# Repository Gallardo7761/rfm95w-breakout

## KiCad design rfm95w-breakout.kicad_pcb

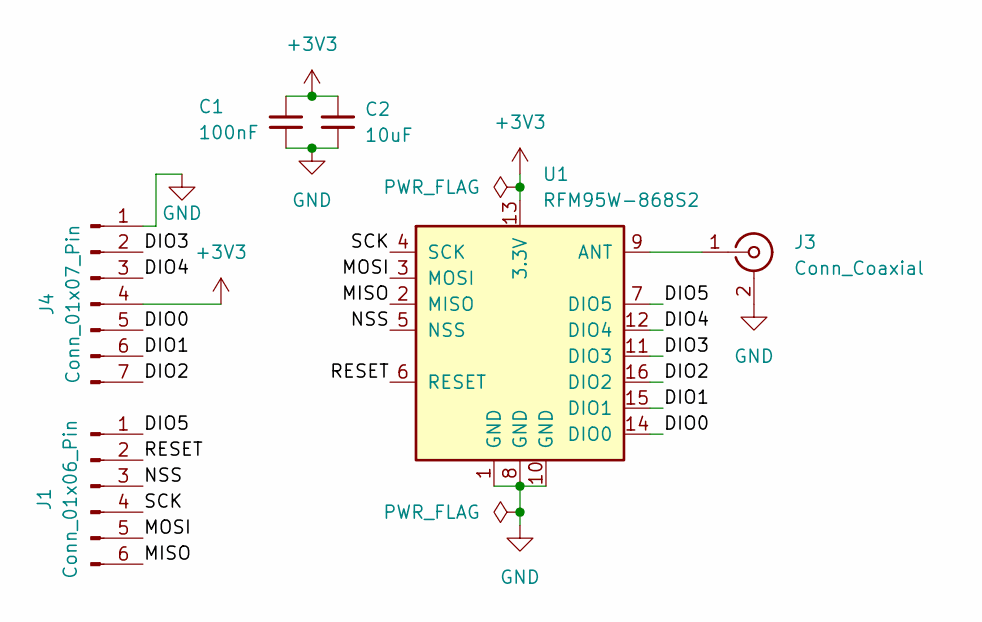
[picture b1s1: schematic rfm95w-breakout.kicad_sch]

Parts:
C1: 100nF; C_0805_2012Metric
C2: 10uF; C_0805_2012Metric
J1: Conn_01x06_Pin; PinHeader_1x06_P2.54mm_Vertical
J3: Conn_Coaxial; SMA_Amphenol_132289_EdgeMount
J4: Conn_01x07_Pin; PinHeader_1x07_P2.54mm_Vertical
U1: RFM95W-868S2; HOPERF_RFM69HW

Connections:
+3V3: C1.1, C2.1, J4.4, U1.13 (3.3V)
/DIO0: J4.5, U1.14 (DIO0)
/DIO1: J4.6, U1.15 (DIO1)
/DIO2: J4.7, U1.16 (DIO2)
/DIO3: J4.2, U1.11 (DIO3)
/DIO4: J4.3, U1.12 (DIO4)
/DIO5: J1.1, U1.7 (DIO5)
/MISO: J1.6, U1.2 (MISO)
/MOSI: J1.5, U1.3 (MOSI)
/NSS: J1.3, U1.5 (NSS)
/RESET: J1.2, U1.6 (RESET)
/SCK: J1.4, U1.4 (SCK)
GND: C1.2, C2.2, J3.2 (Ext), J4.1, U1.1 (GND), U1.8 (GND), U1.10 (GND)
unnamed: J3.1 (In), U1.9 (ANT)

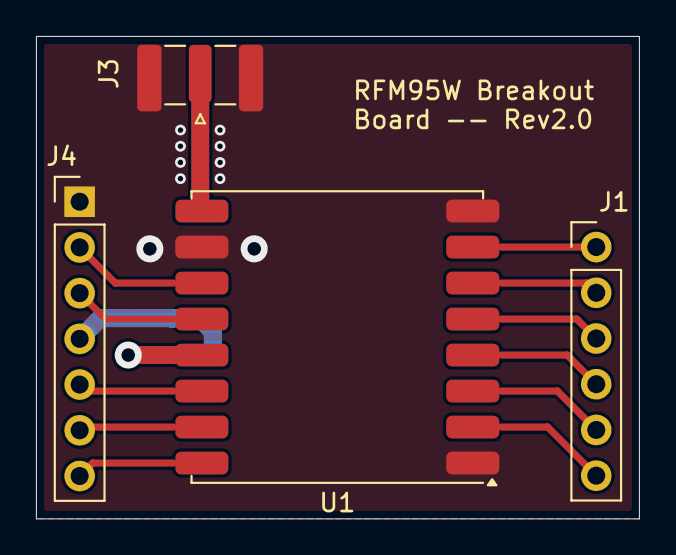
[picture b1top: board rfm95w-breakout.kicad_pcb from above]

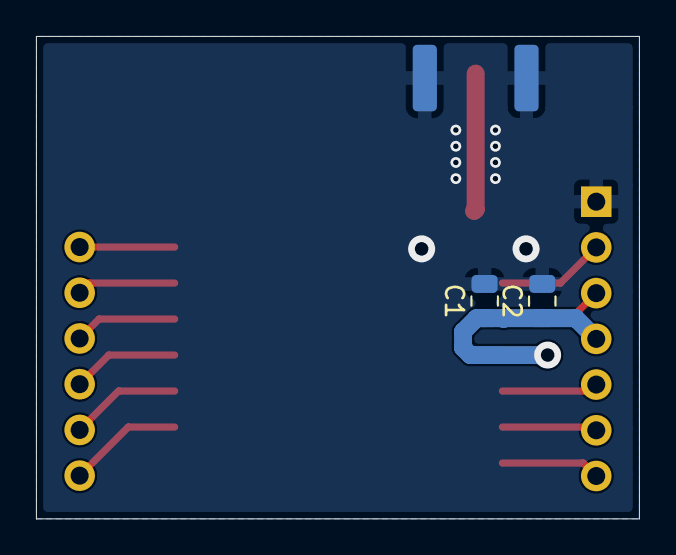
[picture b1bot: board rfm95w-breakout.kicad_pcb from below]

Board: 2 copper layers, 33.5 x 26.8 mm, 6 parts (2 on the bottom side), 14 nets.
